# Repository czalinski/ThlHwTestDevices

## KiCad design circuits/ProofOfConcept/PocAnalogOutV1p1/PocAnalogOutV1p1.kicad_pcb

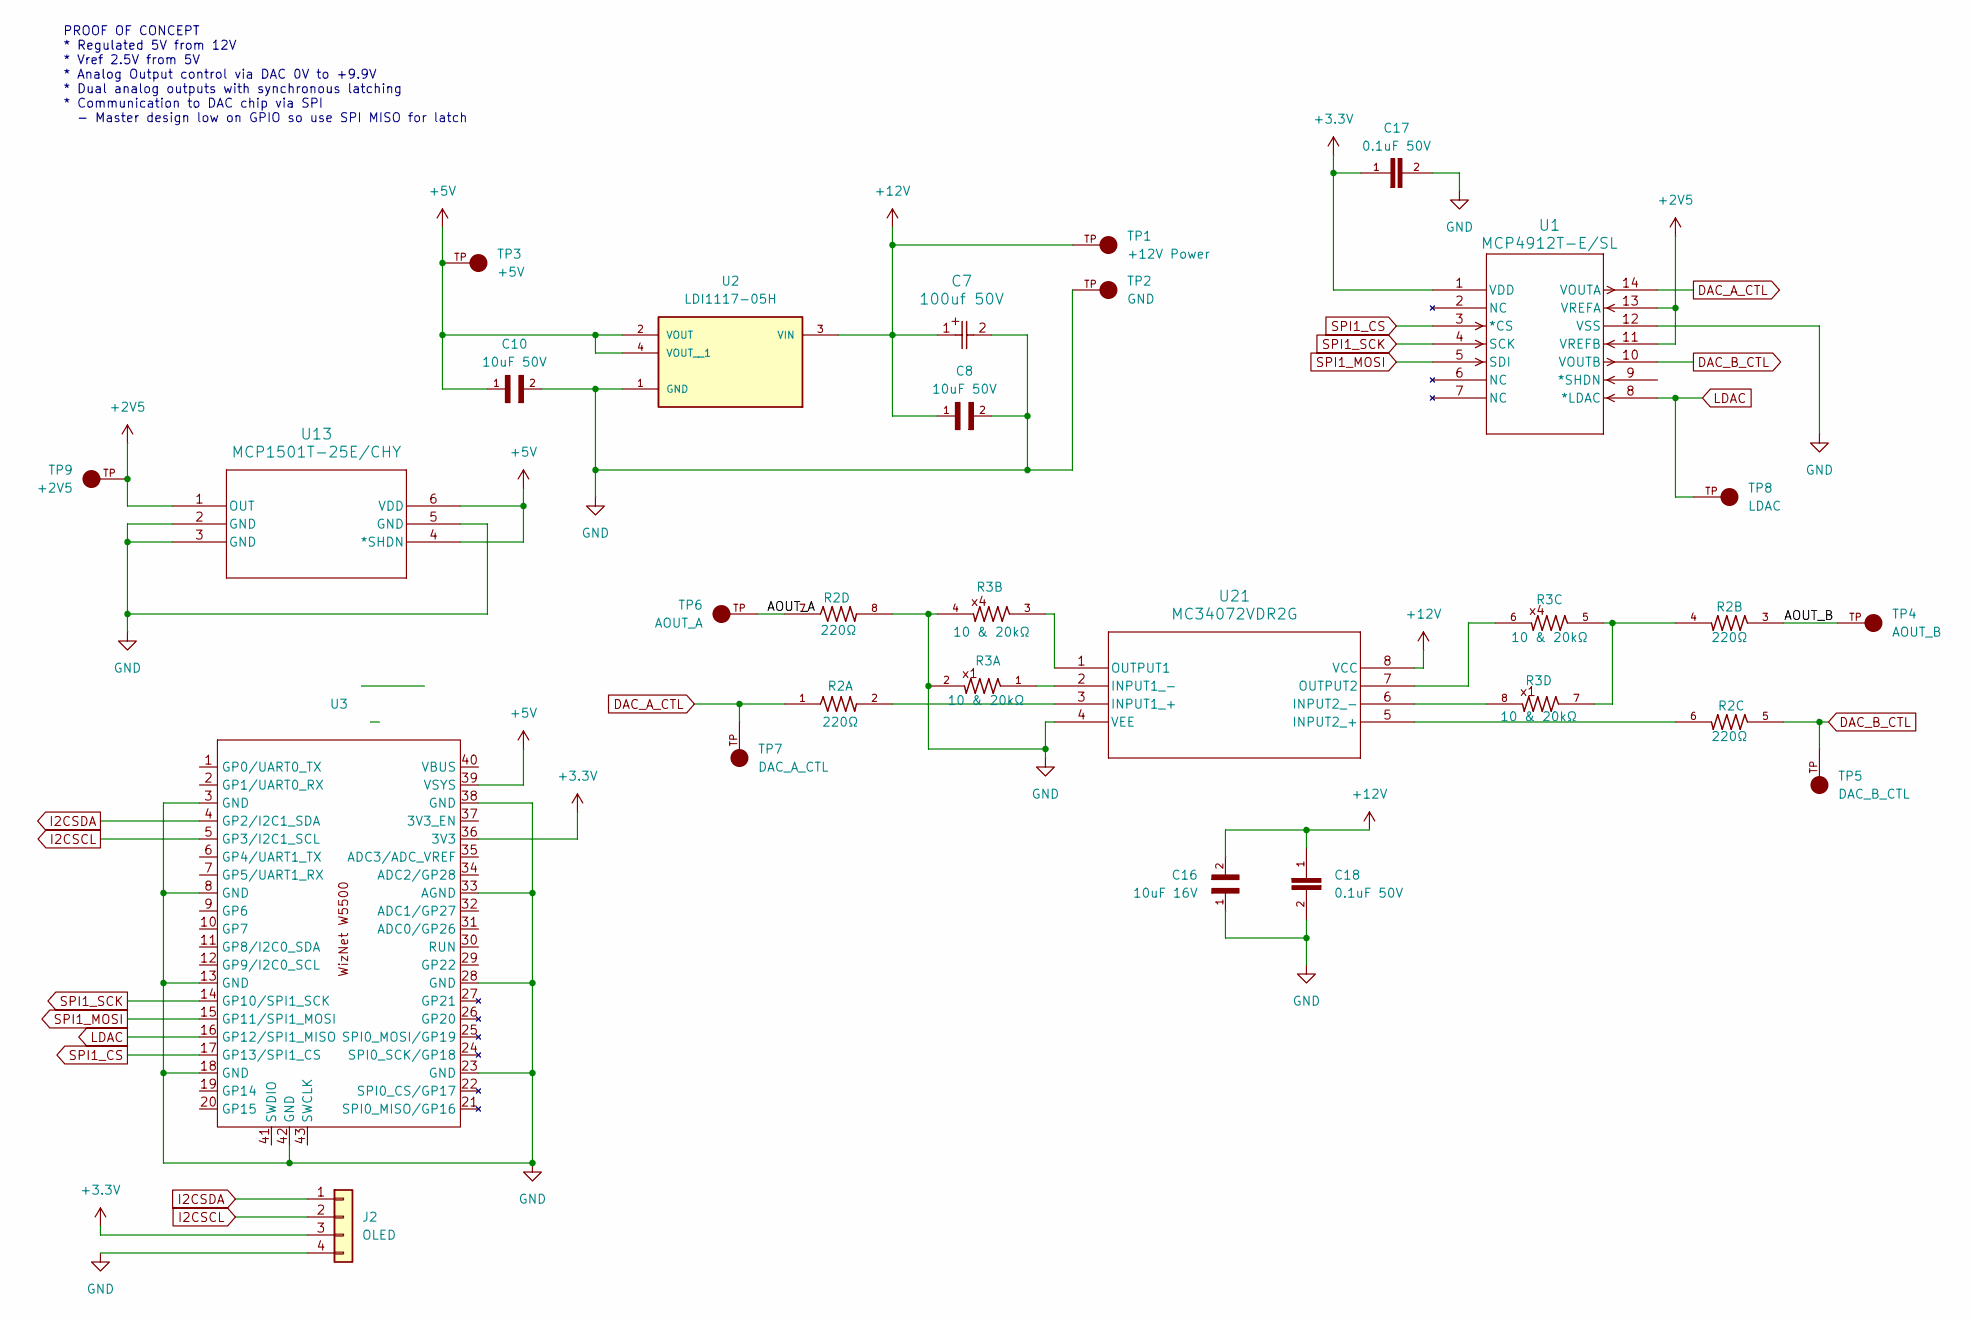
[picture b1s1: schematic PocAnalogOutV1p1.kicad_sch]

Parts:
C7: 100uf 50V; CAP_YX_8X11P5_RUB
C8, C10: 10uF 50V; CAPC3216X180N
C16: 10uF 16V; CAPC2012X140N
C17, C18: 0.1uF 50V; CAPC2012X70
J2: OLED; PinHeader_1x04_P2.54mm_Vertical
R2: 220Ω; RESCAV80P320X160X70-8N
R3: 10 & 20kΩ; RESCAV80P320X160X70-8N
TP1: +12V Power; KEYSTONE_4954_Slot; PARTREV B; DigiKey_Part_Number 36-4954-ND
TP2: GND; KEYSTONE_4954_Slot; PARTREV B; DigiKey_Part_Number 36-4954-ND
TP3: +5V; KEYSTONE_4954_Slot; PARTREV B; DigiKey_Part_Number 36-4954-ND
TP4: AOUT_B; KEYSTONE_4954_Slot; PARTREV B; DigiKey_Part_Number 36-4954-ND
TP5: DAC_B_CTL; KEYSTONE_4954_Slot; PARTREV B; DigiKey_Part_Number 36-4954-ND
TP6: AOUT_A; KEYSTONE_4954_Slot; PARTREV B; DigiKey_Part_Number 36-4954-ND
TP7: DAC_A_CTL; KEYSTONE_4954_Slot; PARTREV B; DigiKey_Part_Number 36-4954-ND
TP8: LDAC; KEYSTONE_4954_Slot; PARTREV B; DigiKey_Part_Number 36-4954-ND
TP9: +2V5; KEYSTONE_4954_Slot; PARTREV B; DigiKey_Part_Number 36-4954-ND
U1: MCP4912T-E/SL; SOIC14-N_MC_MCH
U2: LDI1117-05H; SOT230P700X165-4N; PARTREV 2023-02-01
U3: WizNetPico_OnBoard
U13: MCP1501T-25E/CHY; SOT-23_OT&slash_OTY_MCH
U21: MC34072VDR2G; SOIC8_ONS

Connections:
+2V5: TP9.TP, U1.11 (VREFB), U1.13 (VREFA), U13.1 (OUT)
+3.3V: C17.1, J2.3, U1.1 (VDD), U3.36 (3V3)
+5V: C10.1, TP3.TP, U2.2 (VOUT), U2.4 (VOUT__1), U3.39 (VSYS), U13.4 (*SHDN), U13.6 (VDD)
+12V: C7.1, C8.1, C16.2, C18.1, TP1.TP, U2.3 (VIN), U21.8 (VCC)
/AOUT_A: R2.7, TP6.TP
/AOUT_B: R2.3, TP4.TP
DAC_A_CTL: R2.1, TP7.TP, U1.14 (VOUTA)
DAC_B_CTL: R2.5, TP5.TP, U1.10 (VOUTB)
GND: C7.2, C8.2, C10.2, C16.1, C17.2, C18.2, J2.4, R2.8, R3.2, R3.4, TP2.TP, U1.12 (VSS), U2.1 (GND), U3.3 (GND), U3.8 (GND), U3.13 (GND), U3.18 (GND), U3.23 (GND), U3.28 (GND), U3.33 (AGND), U3.38 (GND), U3.42 (GND), U13.2 (GND), U13.3 (GND), U13.5 (GND), U21.4 (VEE)
I2CSCL: J2.2, U3.5 (GP3/I2C1_SCL)
I2CSDA: J2.1, U3.4 (GP2/I2C1_SDA)
LDAC: TP8.TP, U1.8 (*LDAC), U3.16 (GP12/SPI1_MISO)
unnamed: R2.4, R3.5, R3.7
unnamed: R2.2, U21.3 (INPUT1_+)
unnamed: R3.1, U21.2 (INPUT1_-)
unnamed: R2.6, U21.5 (INPUT2_+)
unnamed: R3.8, U21.6 (INPUT2_-)
unnamed: R3.3, U21.1 (OUTPUT1)
unnamed: R3.6, U21.7 (OUTPUT2)
SPI1_CS: U1.3 (*CS), U3.17 (GP13/SPI1_CS)
SPI1_MOSI: U1.5 (SDI), U3.15 (GP11/SPI1_MOSI)
SPI1_SCK: U1.4 (SCK), U3.14 (GP10/SPI1_SCK)

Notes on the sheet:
PROOF OF CONCEPT * Regulated 5V from 12V * Vref 2.5V from 5V * Analog Output control via DAC 0V to +9.9V * Dual analog outputs with synchronous latching * Communication to DAC chip via SPI - Master design low on GPIO so use SPI MISO for latch

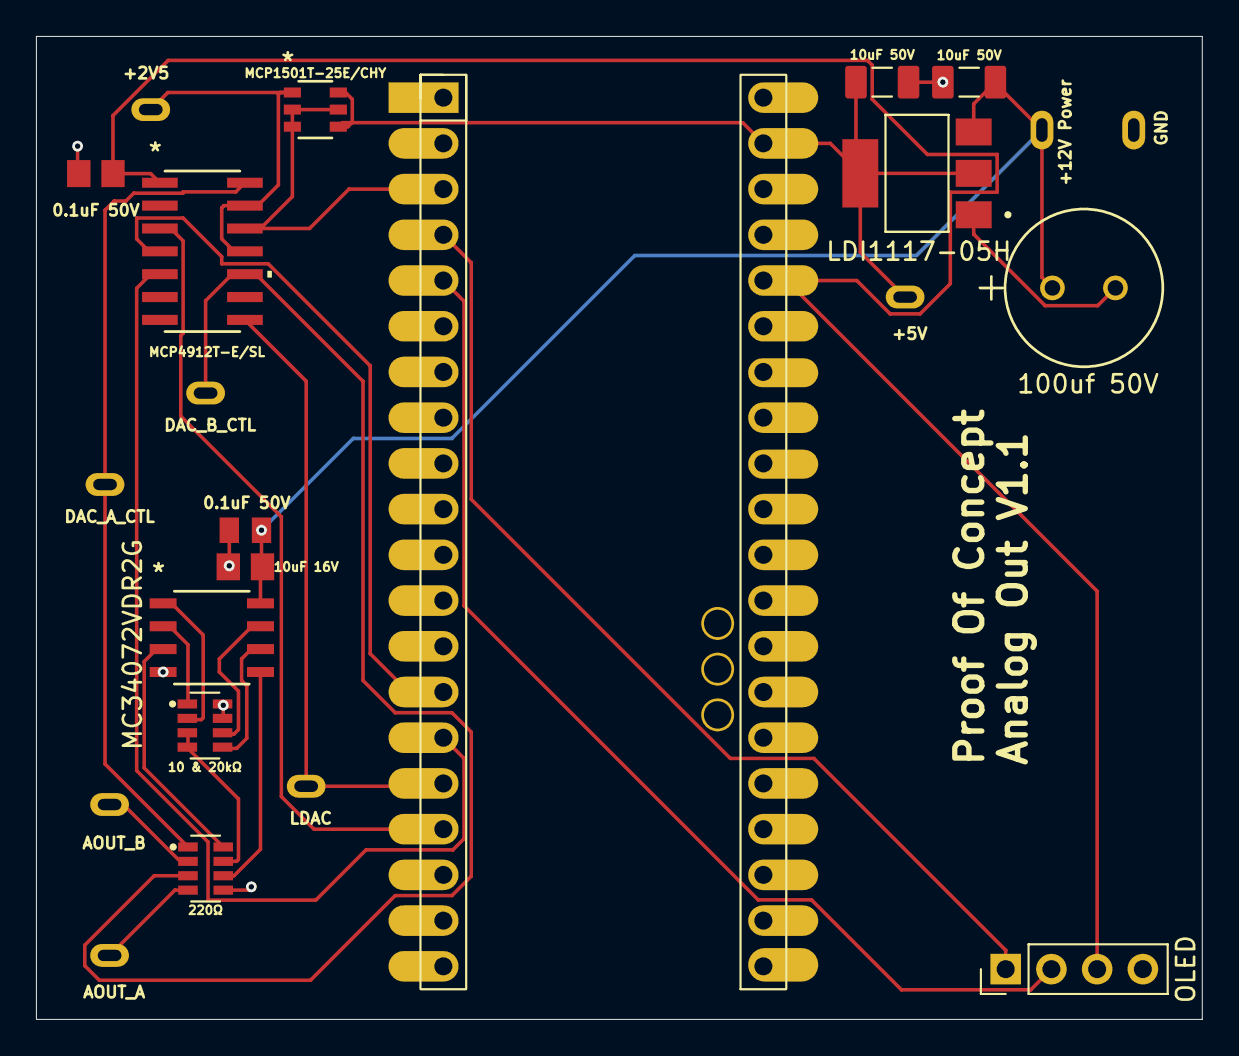
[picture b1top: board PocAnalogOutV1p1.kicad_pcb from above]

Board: 2 copper layers, 64.8 x 54.6 mm, 23 parts (0 on the bottom side), 22 nets.

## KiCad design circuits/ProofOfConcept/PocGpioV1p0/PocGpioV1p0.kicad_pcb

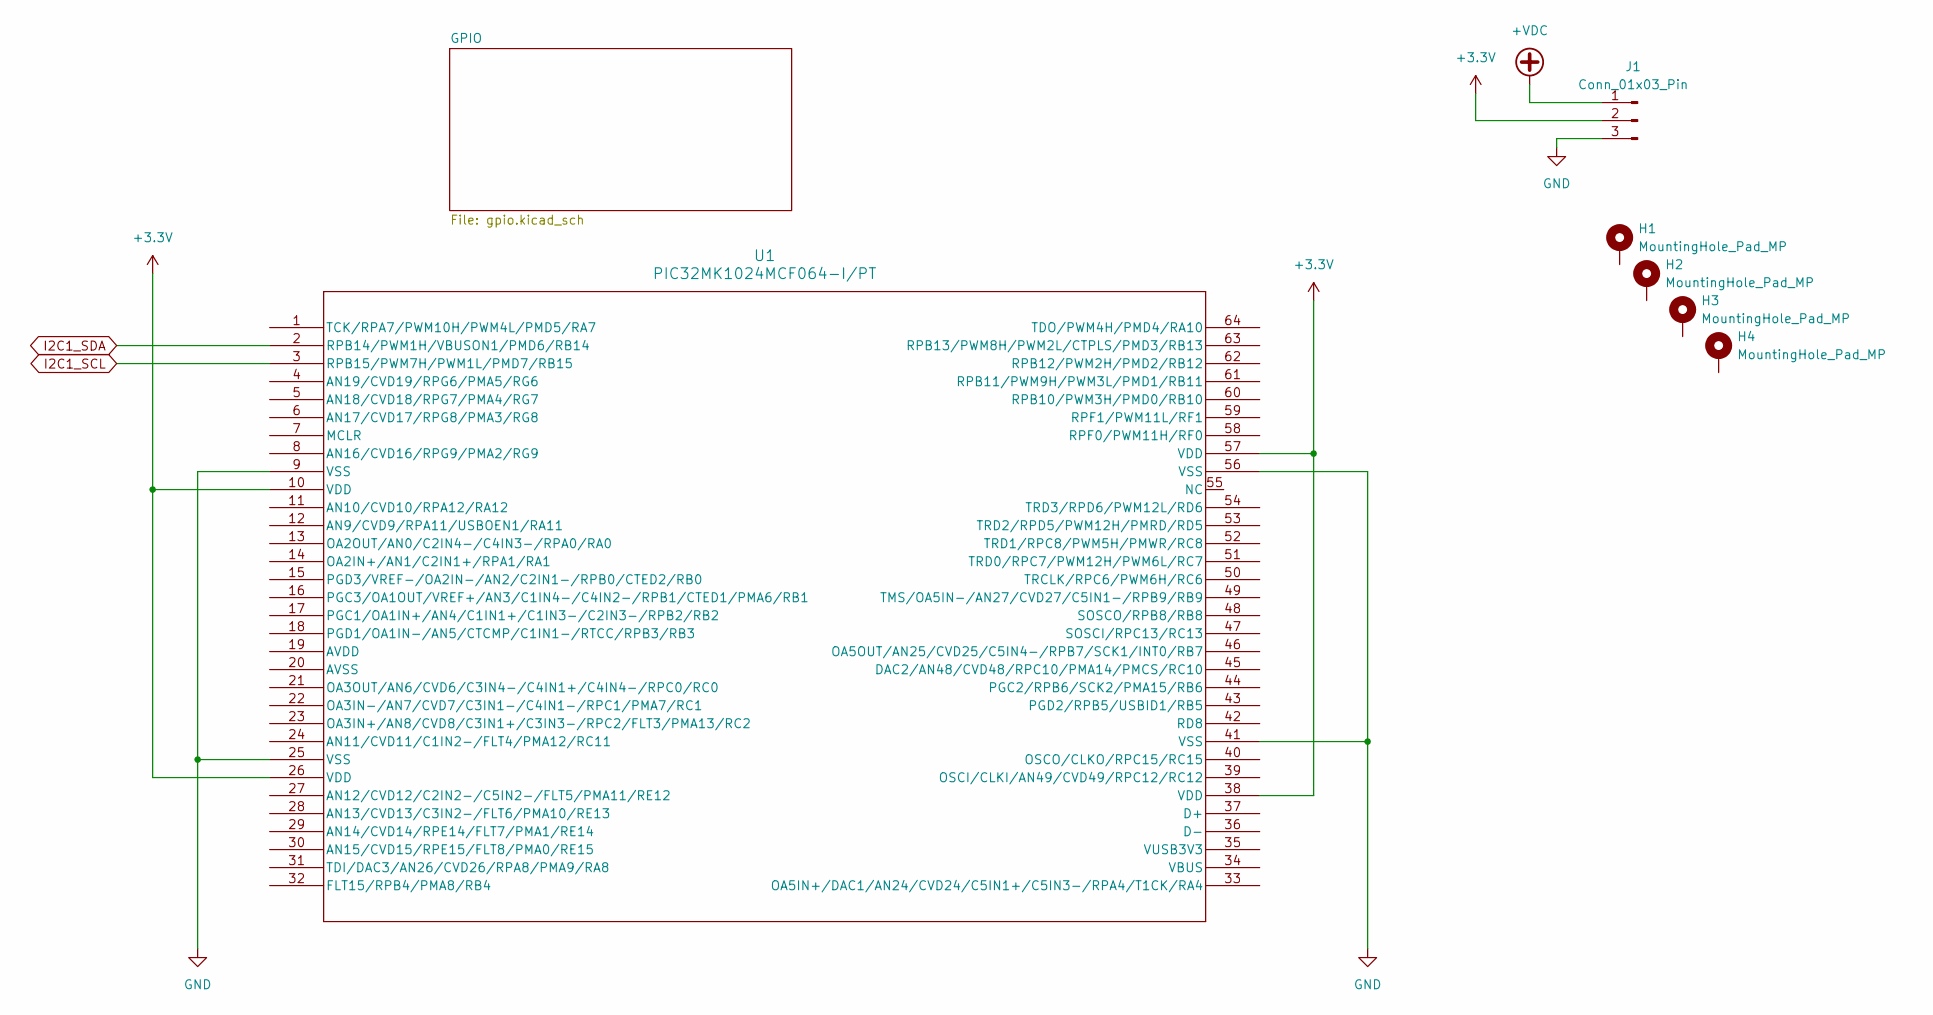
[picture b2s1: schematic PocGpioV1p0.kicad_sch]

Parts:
H1, H2, H3, H4: MountingHole_Pad_MP; MountingHole_3.2mm_M3_Pad_Via
J1: Conn_01x03_Pin; PinHeader_1x03_P2.54mm_Vertical
U1: PIC32MK1024MCF064-I/PT; PIC64_Breakout

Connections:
+3.3V: J1.2, U1.10 (VDD), U1.26 (VDD), U1.38 (VDD), U1.57 (VDD); also elsewhere on the board
+VDC: J1.1; also elsewhere on the board
GND: J1.3, U1.9 (VSS), U1.25 (VSS), U1.41 (VSS), U1.56 (VSS); also elsewhere on the board
I2C1_SCL: U1.3 (RPB15/PWM7H/PWM1L/PMD7/RB15); also elsewhere on the board
I2C1_SDA: U1.2 (RPB14/PWM1H/VBUSON1/PMD6/RB14); also elsewhere on the board

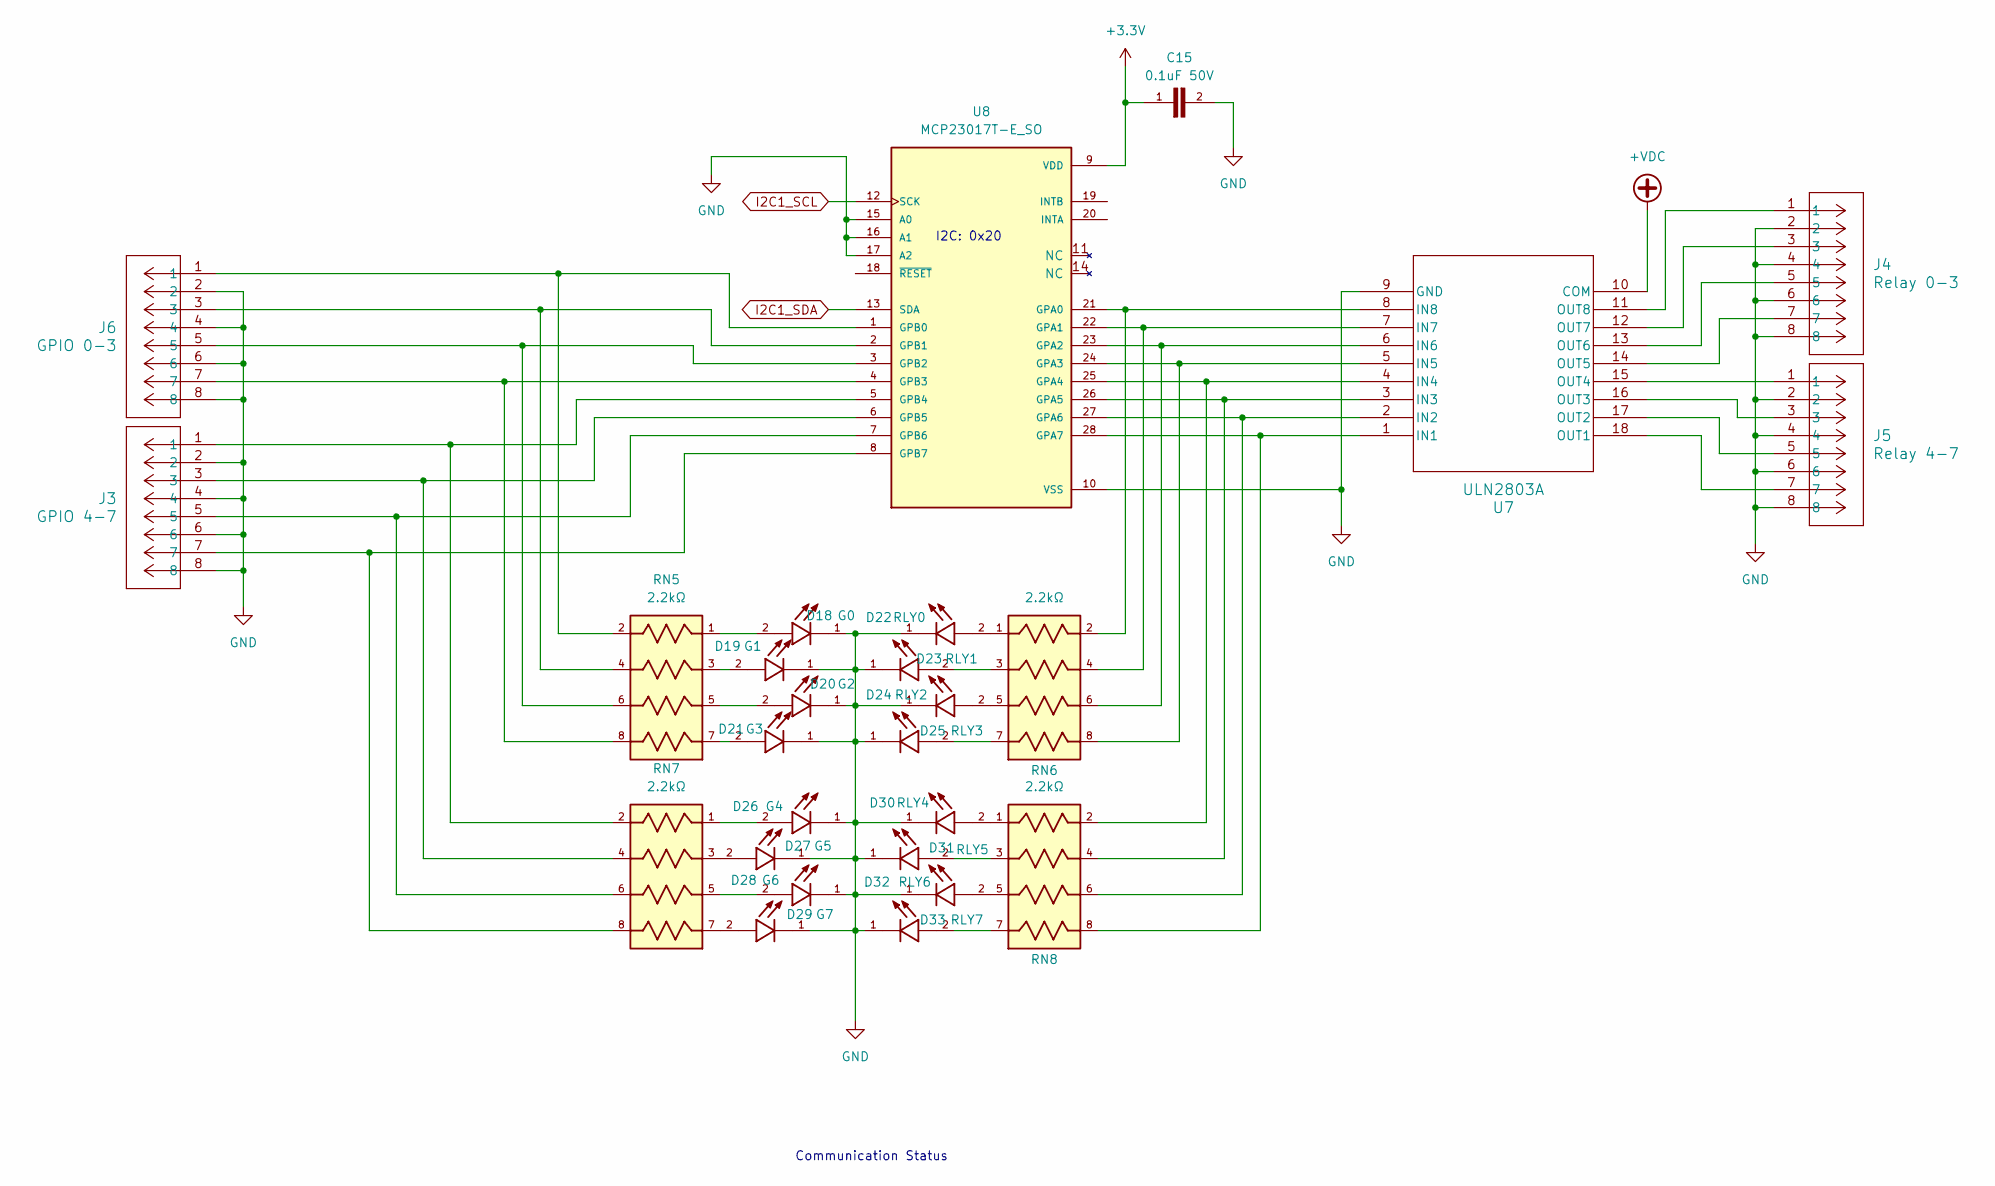
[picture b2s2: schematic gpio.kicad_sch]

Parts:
C15: 0.1uF 50V; CAPC2012X70
D18: G0; LED_LTST-C170GKT; PARTREV I
D19: G1; LED_LTST-C170GKT; PARTREV I
D20: G2; LED_LTST-C170GKT; PARTREV I
D21: G3; LED_LTST-C170GKT; PARTREV I
D22: RLY0; LED_LTST-C170GKT; PARTREV I
D23: RLY1; LED_LTST-C170GKT; PARTREV I
D24: RLY2; LED_LTST-C170GKT; PARTREV I
D25: RLY3; LED_LTST-C170GKT; PARTREV I
D26: G4; LED_LTST-C170GKT; PARTREV I
D27: G5; LED_LTST-C170GKT; PARTREV I
D28: G6; LED_LTST-C170GKT; PARTREV I
D29: G7; LED_LTST-C170GKT; PARTREV I
D30: RLY4; LED_LTST-C170GKT; PARTREV I
D31: RLY5; LED_LTST-C170GKT; PARTREV I
D32: RLY6; LED_LTST-C170GKT; PARTREV I
D33: RLY7; LED_LTST-C170GKT; PARTREV I
J3: GPIO 4-7; CONN_1989803_PXC
J4: Relay 0-3; CONN_1989803_PXC
J5: Relay 4-7; CONN_1989803_PXC
J6: GPIO 0-3; CONN_1989803_PXC
RN5, RN6, RN7, RN8: 2.2kΩ; RESCAXS50P200X100X55-8N
U7: ULN2803A; SOIC-18W_7.5x11.6mm_P1.27mm
U8: MCP23017T-E_SO; SOIC127P1030X265-28N

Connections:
+3.3V: C15.1, U8.9 (VDD); also elsewhere on the board
+VDC: U7.10 (COM); also elsewhere on the board
GND: C15.2, D18.1, D19.1, D20.1, D21.1, D22.1, D23.1, D24.1, D25.1, D26.1, D27.1, D28.1, D29.1, D30.1, D31.1, D32.1, D33.1, J3.2, J3.4, J3.6, J3.8, J4.2, J4.4, J4.6, J4.8, J5.2, J5.4, J5.6, J5.8, J6.2, J6.4, J6.6, J6.8, U7.9 (GND), U8.10 (VSS), U8.15 (A0), U8.16 (A1), U8.17 (A2); also elsewhere on the board
I2C1_SCL: U8.12 (SCK); also elsewhere on the board
I2C1_SDA: U8.13 (SDA); also elsewhere on the board
unnamed: D18.2, RN5.1
unnamed: D19.2, RN5.3
unnamed: D20.2, RN5.5
unnamed: D21.2, RN5.7
unnamed: D22.2, RN6.1
unnamed: D23.2, RN6.3
unnamed: D24.2, RN6.5
unnamed: D25.2, RN6.7
unnamed: D26.2, RN7.1
unnamed: D27.2, RN7.3
unnamed: D28.2, RN7.5
unnamed: D29.2, RN7.7
unnamed: D30.2, RN8.1
unnamed: D31.2, RN8.3
unnamed: D32.2, RN8.5
unnamed: D33.2, RN8.7
unnamed: RN8.8, U7.1 (IN1), U8.28 (GPA7)
unnamed: RN8.6, U7.2 (IN2), U8.27 (GPA6)
unnamed: RN8.4, U7.3 (IN3), U8.26 (GPA5)
unnamed: RN8.2, U7.4 (IN4), U8.25 (GPA4)
unnamed: RN6.8, U7.5 (IN5), U8.24 (GPA3)
unnamed: RN6.6, U7.6 (IN6), U8.23 (GPA2)
unnamed: RN6.4, U7.7 (IN7), U8.22 (GPA1)
unnamed: RN6.2, U7.8 (IN8), U8.21 (GPA0)
unnamed: J5.7, U7.18 (OUT1)
unnamed: J5.5, U7.17 (OUT2)
unnamed: J5.3, U7.16 (OUT3)
unnamed: J5.1, U7.15 (OUT4)
unnamed: J4.7, U7.14 (OUT5)
unnamed: J4.5, U7.13 (OUT6)
unnamed: J4.3, U7.12 (OUT7)
unnamed: J4.1, U7.11 (OUT8)
unnamed: J6.1, RN5.2, U8.1 (GPB0)
unnamed: J6.3, RN5.4, U8.2 (GPB1)
unnamed: J6.5, RN5.6, U8.3 (GPB2)
unnamed: J6.7, RN5.8, U8.4 (GPB3)
unnamed: J3.1, RN7.2, U8.5 (GPB4)
unnamed: J3.3, RN7.4, U8.6 (GPB5)
unnamed: J3.5, RN7.6, U8.7 (GPB6)
unnamed: J3.7, RN7.8, U8.8 (GPB7)

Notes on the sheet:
I2C: 0x20
Communication Status

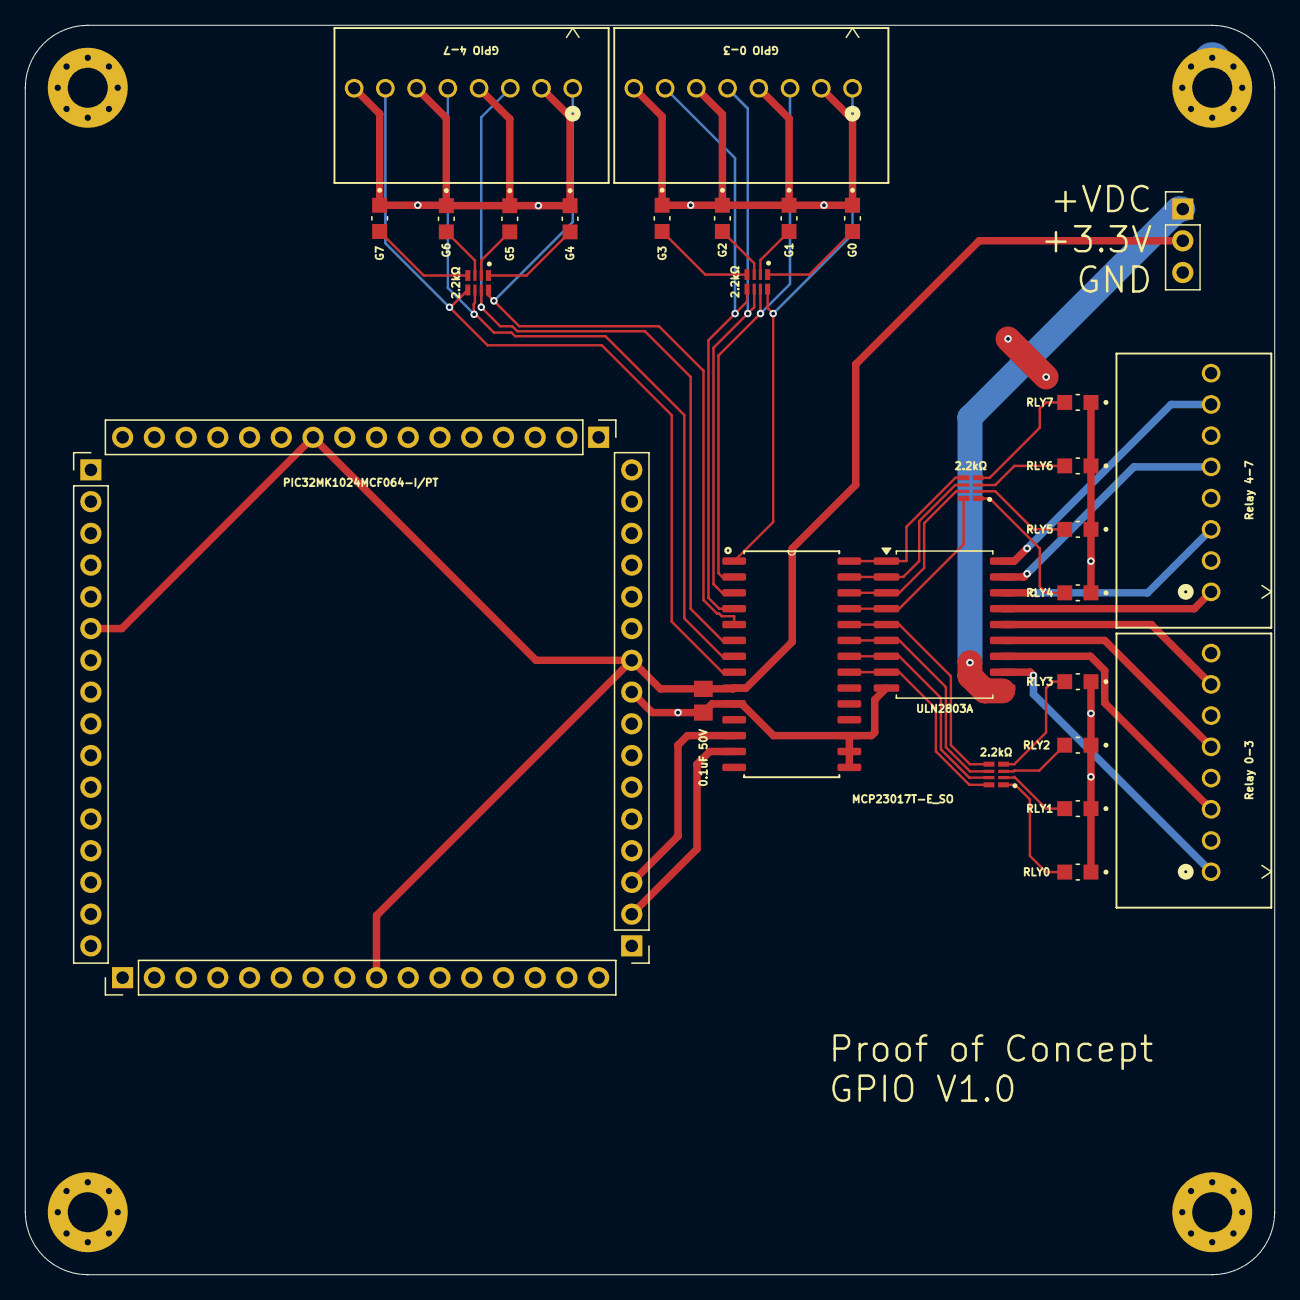
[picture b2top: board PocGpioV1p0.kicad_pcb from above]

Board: 2 copper layers, 100.0 x 100.0 mm, 33 parts (0 on the bottom side), 45 nets.

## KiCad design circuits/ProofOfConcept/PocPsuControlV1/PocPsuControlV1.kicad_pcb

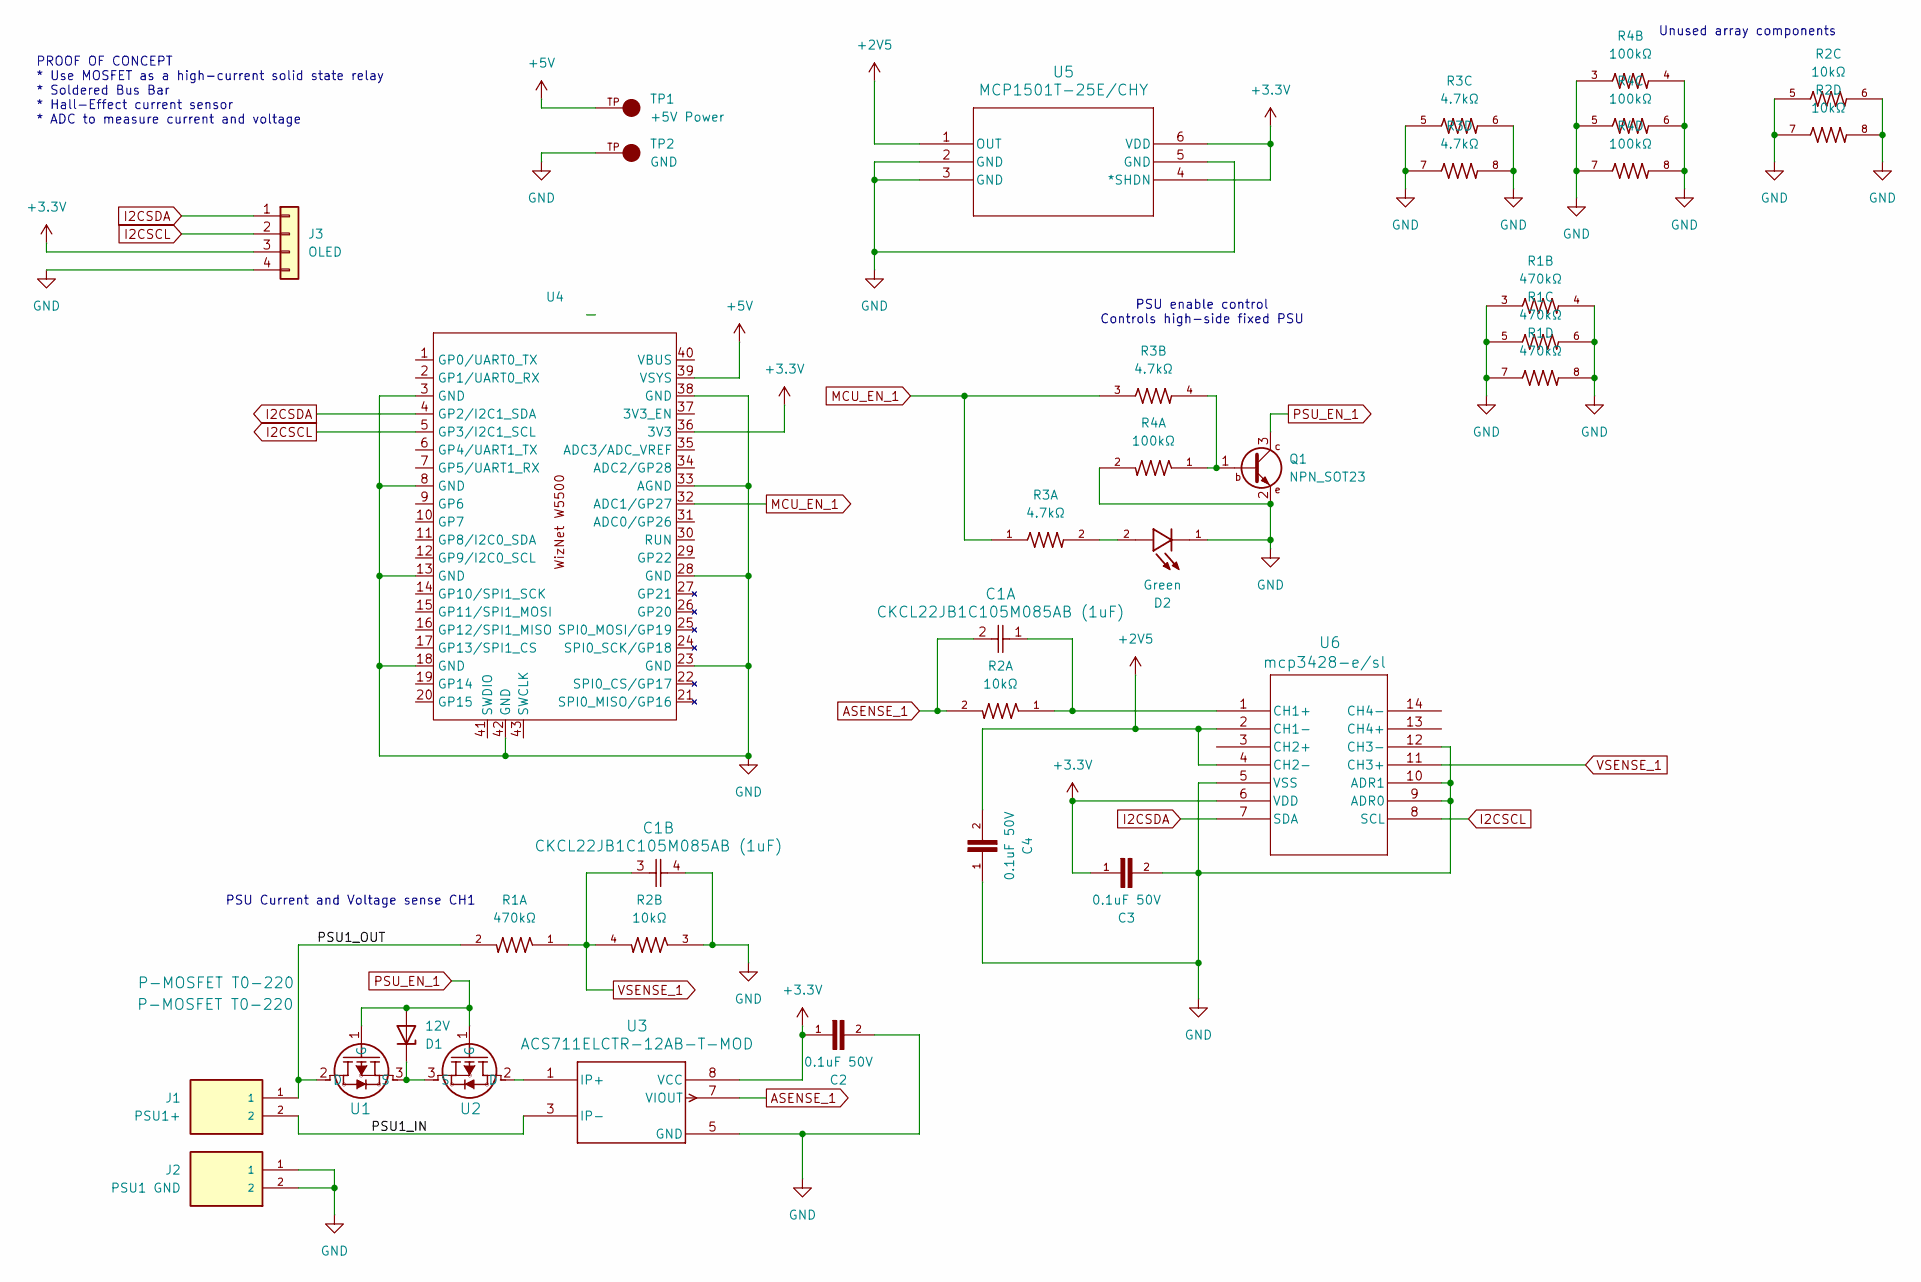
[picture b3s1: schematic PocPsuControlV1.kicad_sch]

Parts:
C1: CKCL22JB1C105M085AB (1uF); CAP_CKCL22_TDK
C2, C3, C4: 0.1uF 50V; CAPC2012X70
D1: 12V; SOD-123_ONS
D2: Green; LED_LTST-C170GKT; PARTREV I
J1: PSU1+; CUI_TB005-762-02BE_BusBar
J2: PSU1 GND; CUI_TB005-762-02BE_BusBar
J3: OLED; PinHeader_1x04_P2.54mm_Vertical
Q1: NPN_SOT23; SOT-23_ONS-L
R1: 470kΩ; RESCAV80P320X160X70-8N
R2: 10kΩ; RESCAV80P320X160X70-8N
R3: 4.7kΩ; RESCAV80P320X160X70-8N
R4: 100kΩ; RESCAV80P320X160X70-8N
TP1: +5V Power; KEYSTONE_4954; PARTREV B; DigiKey_Part_Number 36-4954-ND
TP2: GND; KEYSTONE_4954; PARTREV B; DigiKey_Part_Number 36-4954-ND
U1, U2: P-MOSFET T0-220; TO220AB_VIS
U3: ACS711ELCTR-12AB-T-MOD; SOICN-8_ALM_MOD
U4: WizNetPico_OnBoard
U5: MCP1501T-25E/CHY; SOT-23_OT&slash_OTY_MCH
U6: mcp3428-e/sl; SOIC14-N_MC_MCH

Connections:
+2V5: C4.2, U5.1 (OUT), U6.2 (CH1-), U6.4 (CH2-)
+3.3V: C2.1, C3.1, J3.3, U3.8 (VCC), U4.36 (3V3), U5.4 (*SHDN), U5.6 (VDD), U6.6 (VDD)
+5V: TP1.TP, U4.39 (VSYS)
/PSU1_IN: J1.2, U3.3 (IP-)
/PSU1_OUT: J1.1, R1.2, U1.2 (D)
ASENSE_1: C1.2, R2.2, U3.7 (VIOUT)
GND: C1.4, C2.2, C3.2, C4.1, D2.1, J2.1, J2.2, J3.4, Q1.2 (E), R1.3, R1.4, R1.5, R1.6, R1.7, R1.8, R2.3, R2.5, R2.6, R2.7, R2.8, R3.5, R3.6, R3.7, R3.8, R4.2, R4.3, R4.4, R4.5, R4.6, R4.7, R4.8, TP2.TP, U3.5 (GND), U4.3 (GND), U4.8 (GND), U4.13 (GND), U4.18 (GND), U4.23 (GND), U4.28 (GND), U4.33 (AGND), U4.38 (GND), U4.42 (GND), U5.2 (GND), U5.3 (GND), U5.5 (GND), U6.5 (VSS), U6.9 (ADR0), U6.10 (ADR1), U6.12 (CH3-)
I2CSCL: J3.2, U4.5 (GP3/I2C1_SCL), U6.8 (SCL)
I2CSDA: J3.1, U4.4 (GP2/I2C1_SDA), U6.7 (SDA)
MCU_EN_1: R3.1, R3.3, U4.32 (ADC1/GP27)
unnamed: D1.1 (K), U1.3 (S), U2.3 (S)
unnamed: D2.2, R3.2
unnamed: Q1.1 (B), R3.4, R4.1
unnamed: U2.2 (D), U3.1 (IP+)
unnamed: C1.1, R2.1, U6.1 (CH1+)
PSU_EN_1: D1.2 (A), Q1.3 (C), U1.1 (G), U2.1 (G)
VSENSE_1: C1.3, R1.1, R2.4, U6.11 (CH3+)

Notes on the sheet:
PROOF OF CONCEPT * Use MOSFET as a high-current solid state relay * Soldered Bus Bar * Hall-Effect current sensor * ADC to measure current and voltage
Unused array components
PSU enable control Controls high-side fixed PSU
PSU Current and Voltage sense CH1

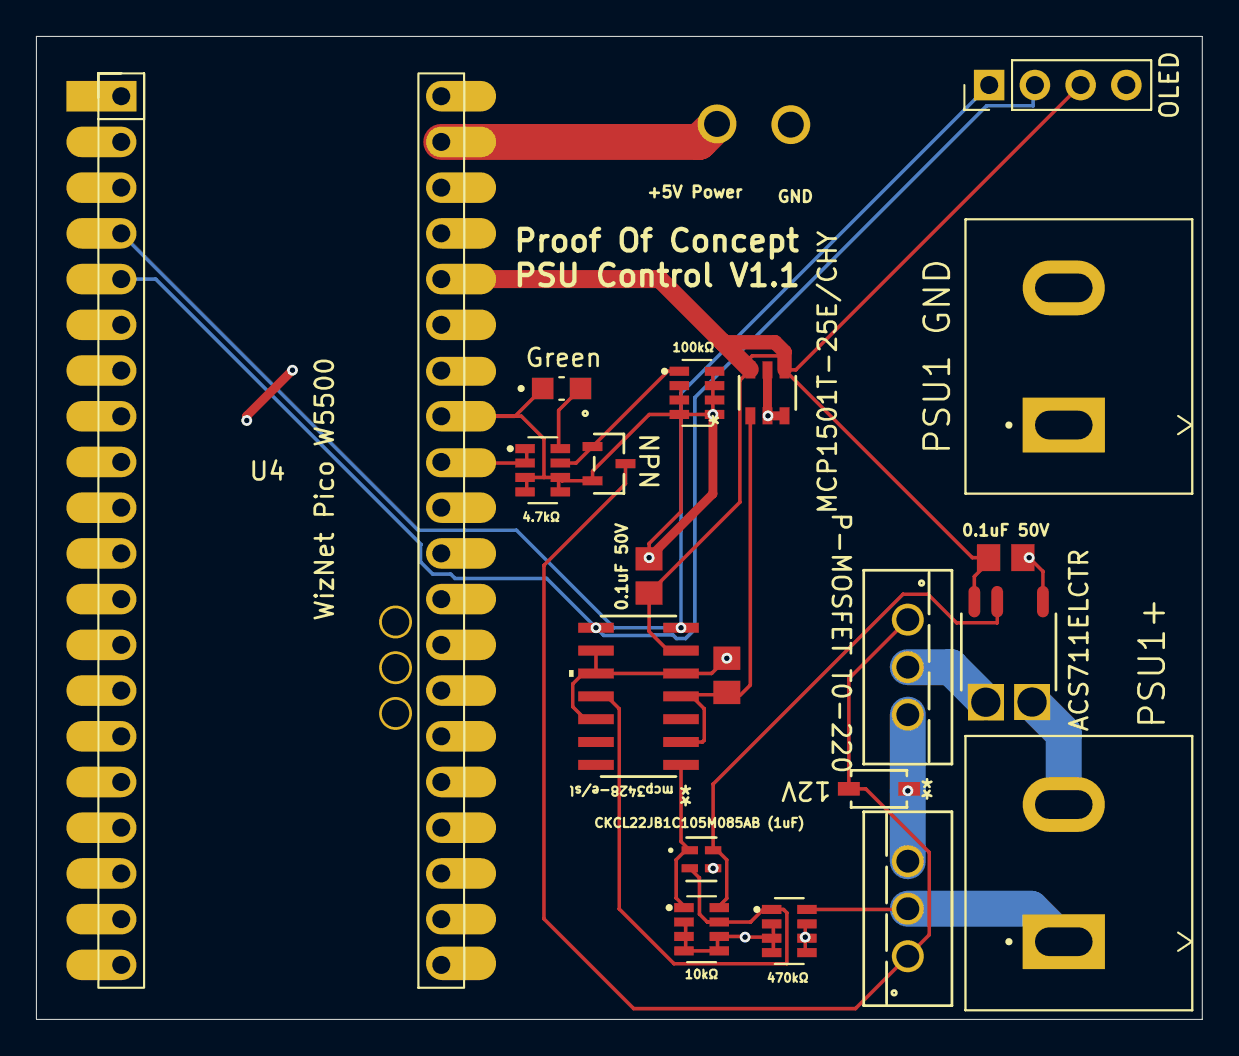
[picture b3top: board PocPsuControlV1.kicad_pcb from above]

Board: 2 copper layers, 64.8 x 54.6 mm, 22 parts (0 on the bottom side), 17 nets.

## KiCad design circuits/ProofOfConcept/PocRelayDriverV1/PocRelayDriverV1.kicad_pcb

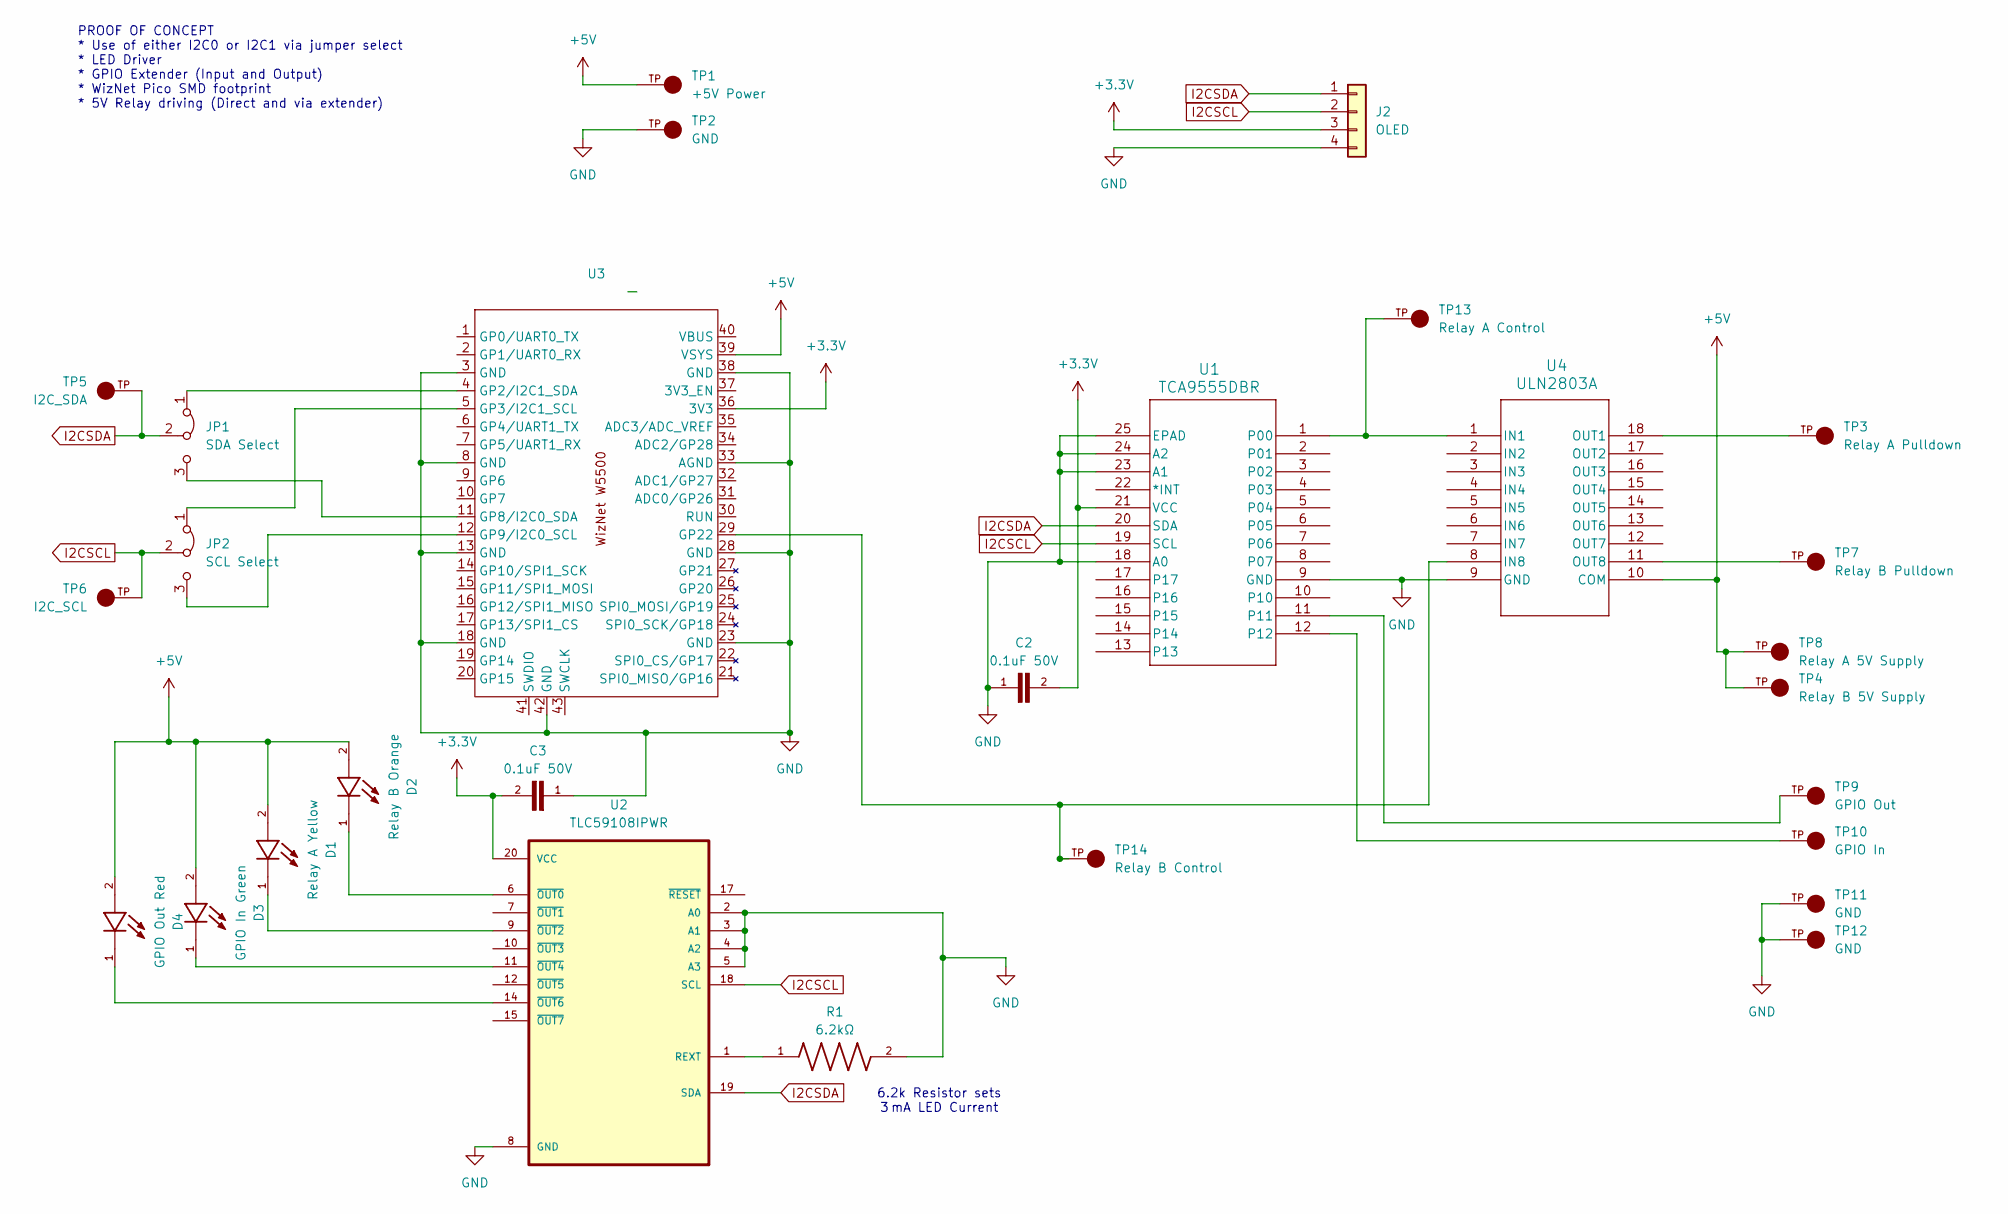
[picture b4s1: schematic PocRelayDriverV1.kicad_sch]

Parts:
C2, C3: 0.1uF 50V; CAPC2012X70
D1: Relay A Yellow; LED_LTST-C170GKT; PARTREV I
D2: Relay B Orange; LED_LTST-C170GKT; PARTREV I
D3: GPIO In Green; LED_LTST-C170GKT; PARTREV I
D4: GPIO Out Red; LED_LTST-C170GKT; PARTREV I
J2: OLED; PinHeader_1x04_P2.54mm_Vertical
JP1: SDA Select; PinHeader_1x03_P2.54mm_Vertical
JP2: SCL Select; PinHeader_1x03_P2.54mm_Vertical
R1: 6.2kΩ; RES_1206
TP1: +5V Power; KEYSTONE_4954; PARTREV B; DigiKey_Part_Number 36-4954-ND
TP2, TP11, TP12: GND; KEYSTONE_4954; PARTREV B; DigiKey_Part_Number 36-4954-ND
TP3: Relay A Pulldown; KEYSTONE_4954; PARTREV B; DigiKey_Part_Number 36-4954-ND
TP4: Relay B 5V Supply; KEYSTONE_4954; PARTREV B; DigiKey_Part_Number 36-4954-ND
TP5: I2C_SDA; KEYSTONE_4954; PARTREV B; DigiKey_Part_Number 36-4954-ND
TP6: I2C_SCL; KEYSTONE_4954; PARTREV B; DigiKey_Part_Number 36-4954-ND
TP7: Relay B Pulldown; KEYSTONE_4954; PARTREV B; DigiKey_Part_Number 36-4954-ND
TP8: Relay A 5V Supply; KEYSTONE_4954; PARTREV B; DigiKey_Part_Number 36-4954-ND
TP9: GPIO Out; KEYSTONE_4954; PARTREV B; DigiKey_Part_Number 36-4954-ND
TP10: GPIO In; KEYSTONE_4954; PARTREV B; DigiKey_Part_Number 36-4954-ND
TP13: Relay A Control; KEYSTONE_4954; PARTREV B; DigiKey_Part_Number 36-4954-ND
TP14: Relay B Control; KEYSTONE_4954; PARTREV B; DigiKey_Part_Number 36-4954-ND
U1: TCA9555DBR; RTW24_2P45X2P45_TEX
U2: TLC59108IPWR; SOP65P640X120-20N; DigiKey_Part_Number 296-25340-1-ND
U3: WizNetPico_OnBoard
U4: ULN2803A; DIP-18_STM

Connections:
+3.3V: C2.2, C3.2, J2.3, U1.21 (VCC), U2.20 (VCC), U3.36 (3V3)
+5V: D1.2, D2.2, D3.2, D4.2, TP1.TP, TP4.TP, TP8.TP, U3.39 (VSYS), U4.10 (COM)
GND: C2.1, C3.1, J2.4, R1.2, TP2.TP, TP11.TP, TP12.TP, U1.9 (GND), U1.18 (A0), U1.23 (A1), U1.24 (A2), U1.25 (EPAD), U2.2 (A0), U2.3 (A1), U2.4 (A2), U2.5 (A3), U2.8 (GND), U2.13 (GND), U2.16 (GND), U3.3 (GND), U3.8 (GND), U3.13 (GND), U3.18 (GND), U3.23 (GND), U3.28 (GND), U3.33 (AGND), U3.38 (GND), U3.42 (GND), U4.9 (GND)
I2CSCL: J2.2, JP2.2 (C), TP6.TP, U1.19 (SCL), U2.18 (SCL)
I2CSDA: J2.1, JP1.2 (C), TP5.TP, U1.20 (SDA), U2.19 (SDA)
unnamed: JP1.1 (A), U3.4 (GP2/I2C1_SDA)
unnamed: JP1.3 (B), U3.11 (GP8/I2C0_SDA)
unnamed: JP2.1 (A), U3.5 (GP3/I2C1_SCL)
unnamed: JP2.3 (B), U3.12 (GP9/I2C0_SCL)
unnamed: TP13.TP, U1.1 (P00), U4.1 (IN1)
unnamed: TP9.TP, U1.11
unnamed: TP10.TP, U1.12
unnamed: R1.1, U2.1 (REXT)
unnamed: D2.1, U2.6 (~OUT0)
unnamed: D1.1, U2.9 (~OUT2)
unnamed: D3.1, U2.11 (~OUT4)
unnamed: D4.1, U2.14 (~OUT6)
unnamed: TP14.TP, U3.29 (GP22), U4.8 (IN8)
unnamed: TP3.TP, U4.18 (OUT1)
unnamed: TP7.TP, U4.11 (OUT8)

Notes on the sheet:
PROOF OF CONCEPT * Use of either I2C0 or I2C1 via jumper select * LED Driver * GPIO Extender (Input and Output) * WizNet Pico SMD footprint * 5V Relay driving (Direct and via extender)
6.2k Resistor sets 3 mA LED Current
